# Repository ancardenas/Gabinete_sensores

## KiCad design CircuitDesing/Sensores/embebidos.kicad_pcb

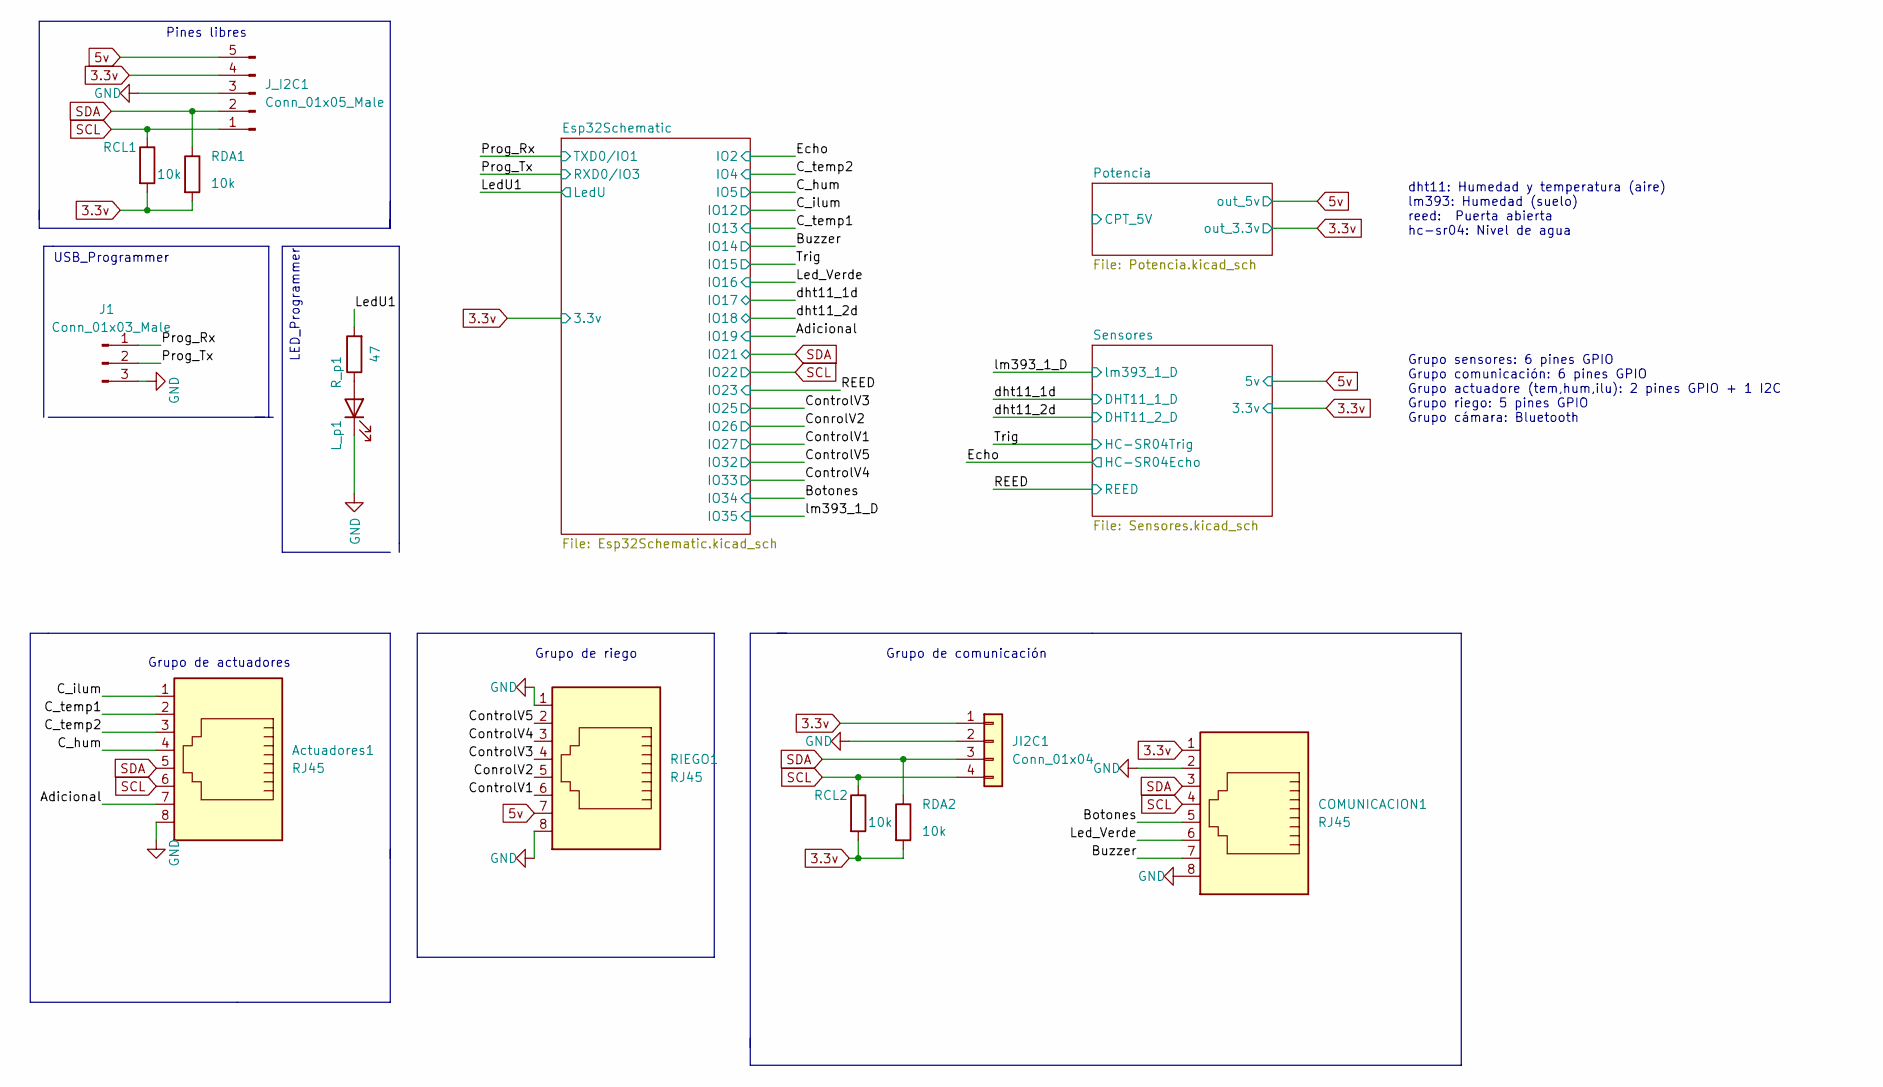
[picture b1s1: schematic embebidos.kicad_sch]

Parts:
Actuadores1: RJ45; RJ45_Amphenol_54602-x08_Horizontal
COMUNICACION1: RJ45; RJ45_Amphenol_54602-x08_Horizontal
J1: Conn_01x03_Male; PinHeader_1x03_P2.54mm_Vertical
JI2C1: Conn_01x04; JST_EH_B4B-EH-A_1x04_P2.50mm_Vertical
J_I2C1: Conn_01x05_Male; PinSocket_1x05_P2.54mm_Horizontal
L_p1: LED; LED_0805_2012Metric_Pad1.15x1.40mm_HandSolder
RCL1, RCL2: 10k; R_0805_2012Metric_Pad1.20x1.40mm_HandSolder
RDA1, RDA2: 10k; R_0805_2012Metric_Pad1.20x1.40mm_HandSolder
RIEGO1: RJ45; RJ45_Amphenol_54602-x08_Horizontal
R_p1: 47; R_0805_2012Metric_Pad1.20x1.40mm_HandSolder

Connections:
3.3v: COMUNICACION1.1, JI2C1.1, J_I2C1.4, RCL1.2, RCL2.2, RDA1.2, RDA2.2; also elsewhere on the board
5v: J_I2C1.5, RIEGO1.7; also elsewhere on the board
/Adicional: Actuadores1.7; also elsewhere on the board
/Botones: COMUNICACION1.5; also elsewhere on the board
/Buzzer: COMUNICACION1.7; also elsewhere on the board
/C_hum: Actuadores1.4; also elsewhere on the board
/C_ilum: Actuadores1.1; also elsewhere on the board
/C_temp1: Actuadores1.2; also elsewhere on the board
/C_temp2: Actuadores1.3; also elsewhere on the board
/ConrolV2: RIEGO1.5; also elsewhere on the board
/ControlV1: RIEGO1.6; also elsewhere on the board
/ControlV3: RIEGO1.4; also elsewhere on the board
/ControlV4: RIEGO1.3; also elsewhere on the board
/ControlV5: RIEGO1.2; also elsewhere on the board
/LedU1: R_p1.2; also elsewhere on the board
/Led_Verde: COMUNICACION1.6; also elsewhere on the board
/Prog_Rx: J1.1; also elsewhere on the board
/Prog_Tx: J1.2; also elsewhere on the board
GND: Actuadores1.8, COMUNICACION1.2, COMUNICACION1.8, J1.3, JI2C1.2, J_I2C1.3, L_p1.1 (K), RIEGO1.1, RIEGO1.8; also elsewhere on the board
unnamed: L_p1.2 (A), R_p1.1
SCL: Actuadores1.6, COMUNICACION1.4, JI2C1.4, J_I2C1.1, RCL1.1, RCL2.1; also elsewhere on the board
SDA: Actuadores1.5, COMUNICACION1.3, JI2C1.3, J_I2C1.2, RDA1.1, RDA2.1; also elsewhere on the board

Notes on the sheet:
Grupo sensores: 6 pines GPIO Grupo comunicación: 6 pines GPIO Grupo actuadore (tem,hum,ilu): 2 pines GPIO + 1 I2C Grupo riego: 5 pines GPIO Grupo cámara: Bluetooth
USB_Programmer
Grupo de actuadores
LED_Programmer
Pines libres
Grupo de comunicación
dht11: Humedad y temperatura (aire) lm393: Humedad (suelo) reed: Puerta abierta hc-sr04: Nivel de agua
Grupo de riego

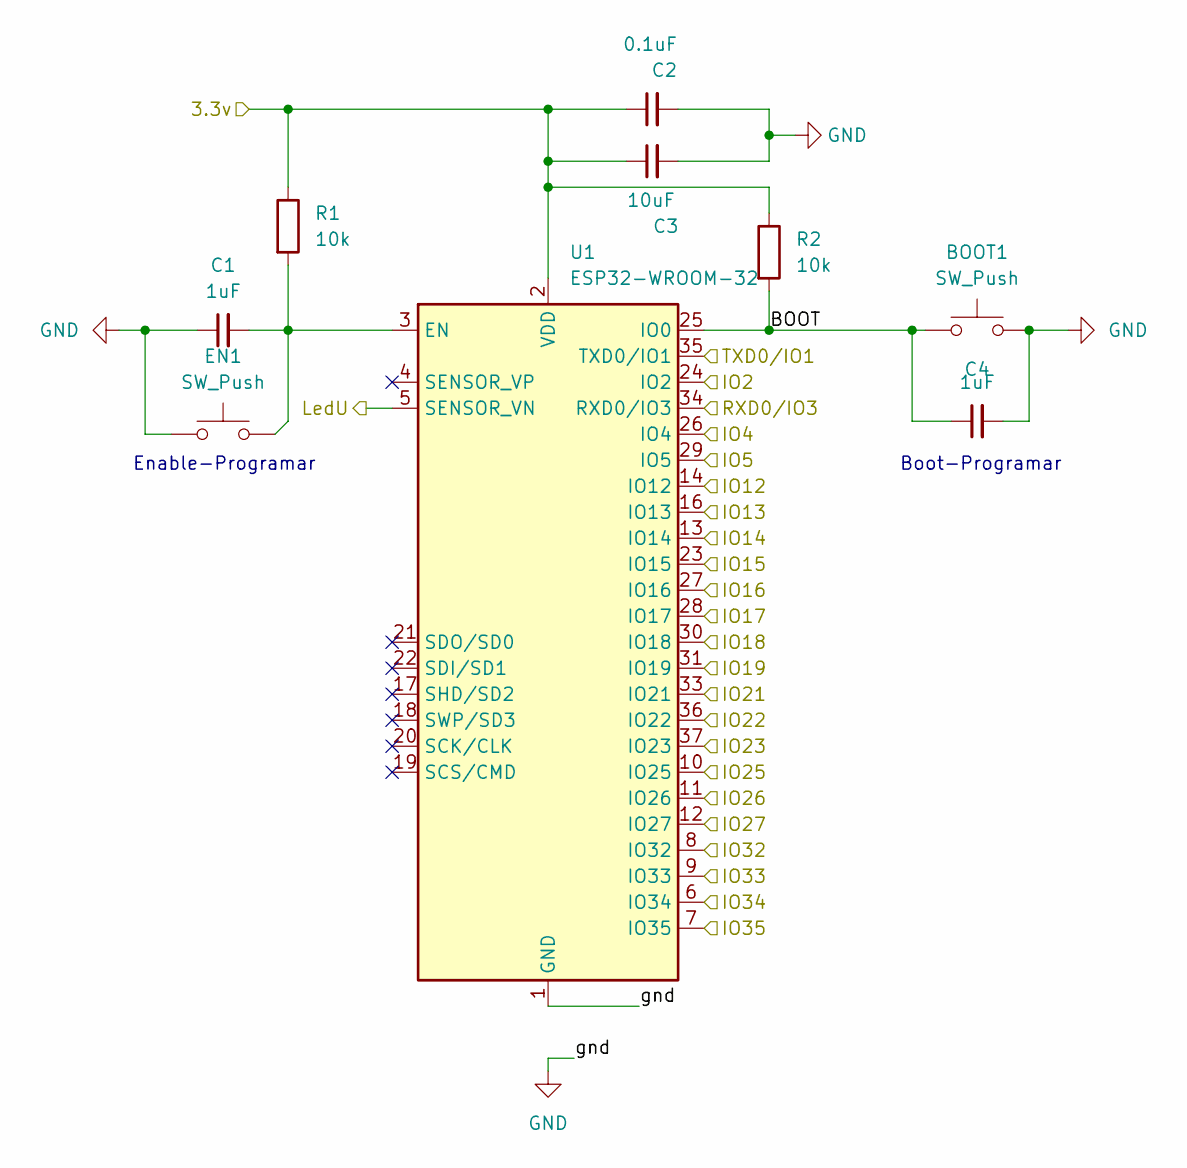
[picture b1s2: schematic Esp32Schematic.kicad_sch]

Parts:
BOOT1: SW_Push; SW_Push_1P1T_NO_6x6mm_H9.5mm
C1, C4: 1uF; C_0603_1608Metric_Pad1.08x0.95mm_HandSolder
C2: 0.1uF; C_0603_1608Metric_Pad1.08x0.95mm_HandSolder
C3: 10uF; C_0603_1608Metric_Pad1.08x0.95mm_HandSolder
EN1: SW_Push; SW_Push_1P1T_NO_6x6mm_H9.5mm
R1, R2: 10k; R_0603_1608Metric_Pad0.98x0.95mm_HandSolder
U1: ESP32-WROOM-32

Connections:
3.3v: C2.1, C3.1, R1.1, R2.1, U1.2 (VDD); also elsewhere on the board
/Adicional: U1.31 (IO19); also elsewhere on the board
/Botones: U1.6 (IO34); also elsewhere on the board
/Buzzer: U1.13 (IO14); also elsewhere on the board
/C_hum: U1.29 (IO5); also elsewhere on the board
/C_ilum: U1.14 (IO12); also elsewhere on the board
/C_temp1: U1.16 (IO13); also elsewhere on the board
/C_temp2: U1.26 (IO4); also elsewhere on the board
/ConrolV2: U1.11 (IO26); also elsewhere on the board
/ControlV1: U1.12 (IO27); also elsewhere on the board
/ControlV3: U1.10 (IO25); also elsewhere on the board
/ControlV4: U1.9 (IO33); also elsewhere on the board
/ControlV5: U1.8 (IO32); also elsewhere on the board
/Echo: U1.24 (IO2); also elsewhere on the board
/Esp32Schematic/BOOT: BOOT1.1, C4.1, R2.2, U1.25 (IO0)
/LedU1: U1.5 (SENSOR_VN); also elsewhere on the board
/Led_Verde: U1.27 (IO16); also elsewhere on the board
/Prog_Rx: U1.35 (TXD0/IO1); also elsewhere on the board
/Prog_Tx: U1.34 (RXD0/IO3); also elsewhere on the board
/REED: U1.37 (IO23); also elsewhere on the board
/Trig: U1.23 (IO15); also elsewhere on the board
/dht11_1d: U1.28 (IO17); also elsewhere on the board
/dht11_2d: U1.30 (IO18); also elsewhere on the board
/lm393_1_D: U1.7 (IO35); also elsewhere on the board
GND: BOOT1.2, C1.1, C2.2, C3.2, C4.2, EN1.1, U1.1 (GND), U1.15 (GND), U1.38 (GND), U1.39 (GND); also elsewhere on the board
unnamed: C1.2, EN1.2, R1.2, U1.3 (EN)
SCL: U1.36 (IO22); also elsewhere on the board
SDA: U1.33 (IO21); also elsewhere on the board

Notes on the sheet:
Enable-Programar
Boot-Programar

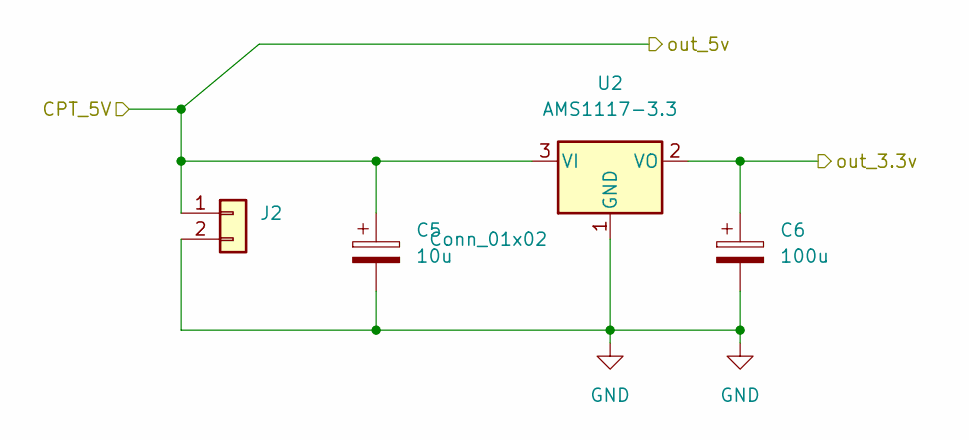
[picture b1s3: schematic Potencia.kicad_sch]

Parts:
C5: 10u; C_0603_1608Metric_Pad1.08x0.95mm_HandSolder
C6: 100u; C_0603_1608Metric_Pad1.08x0.95mm_HandSolder
J2: Conn_01x02; TerminalBlock_bornier-2_P5.08mm
U2: AMS1117-3.3; SOT-223-3_TabPin2

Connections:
3.3v: C6.1, U2.2 (VO); also elsewhere on the board
5v: C5.1, J2.1, U2.3 (VI); also elsewhere on the board
GND: C5.2, C6.2, J2.2, U2.1 (GND); also elsewhere on the board

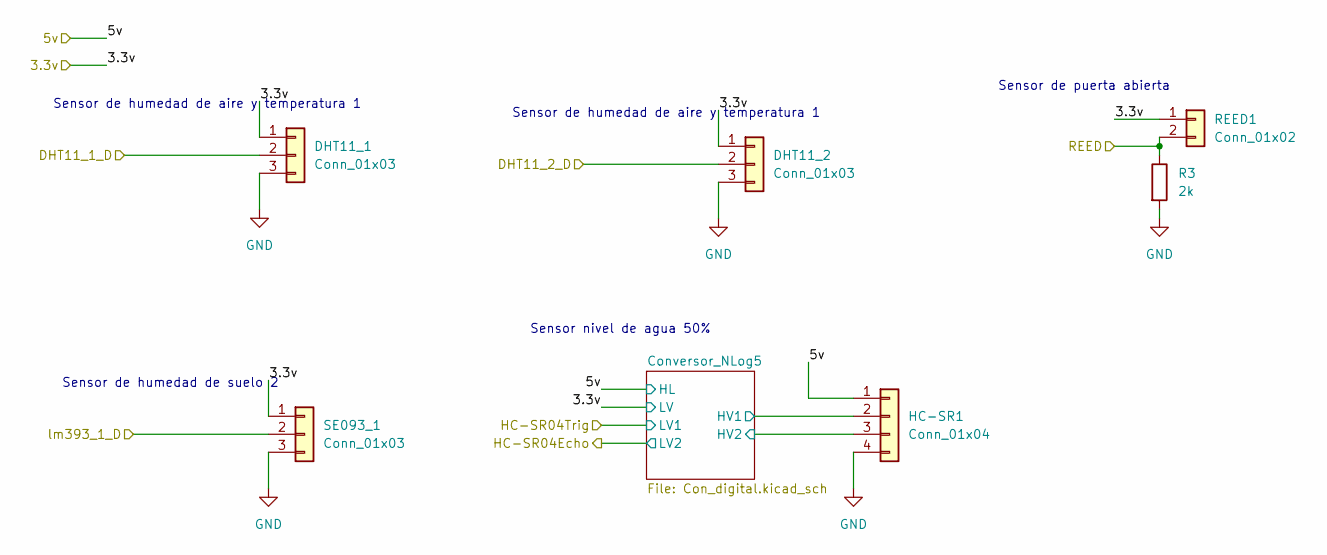
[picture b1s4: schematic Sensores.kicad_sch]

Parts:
DHT11_1, DHT11_2: Conn_01x03; JST_EH_B3B-EH-A_1x03_P2.50mm_Vertical
HC-SR1: Conn_01x04; JST_EH_B4B-EH-A_1x04_P2.50mm_Vertical
R3: 2k; R_0603_1608Metric_Pad0.98x0.95mm_HandSolder
REED1: Conn_01x02; JST_EH_B2B-EH-A_1x02_P2.50mm_Vertical
SE093_1: Conn_01x03; JST_EH_B3B-EH-A_1x03_P2.50mm_Vertical

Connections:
3.3v: DHT11_1.1, DHT11_2.1, REED1.1, SE093_1.1; also elsewhere on the board
5v: HC-SR1.1; also elsewhere on the board
/REED: R3.1, REED1.2; also elsewhere on the board
/Sensores/Conversor_NLog5/HV1: HC-SR1.2; also elsewhere on the board
/Sensores/Conversor_NLog5/HV2: HC-SR1.3; also elsewhere on the board
/dht11_1d: DHT11_1.2; also elsewhere on the board
/dht11_2d: DHT11_2.2; also elsewhere on the board
/lm393_1_D: SE093_1.2; also elsewhere on the board
GND: DHT11_1.3, DHT11_2.3, HC-SR1.4, R3.2, SE093_1.3; also elsewhere on the board

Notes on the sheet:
Sensor de humedad de aire y temperatura 1
Sensor nivel de agua 50%
Sensor de humedad de suelo 2
Sensor de puerta abierta

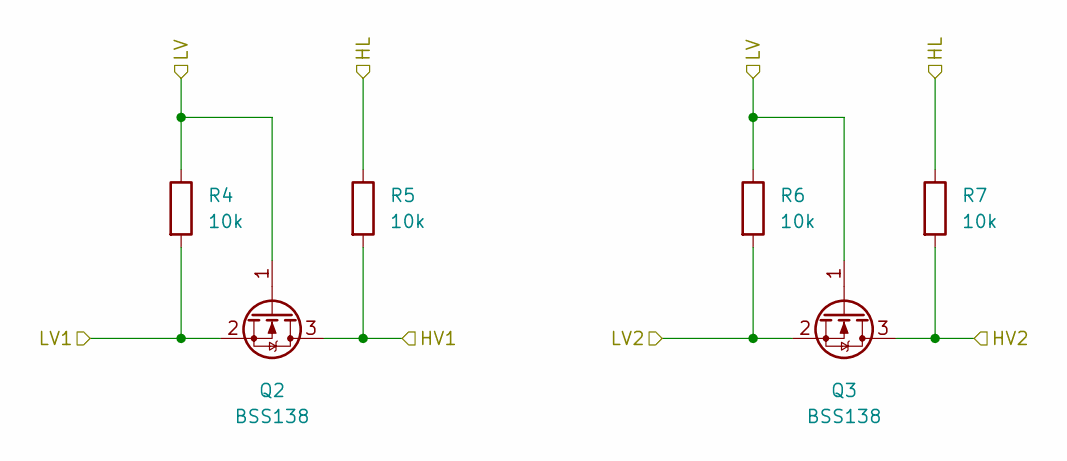
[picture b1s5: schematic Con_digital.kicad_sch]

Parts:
Q2, Q3: BSS138; SOT-23
R4, R5, R6, R7: 10k; R_0603_1608Metric_Pad0.98x0.95mm_HandSolder

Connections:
3.3v: Q2.1 (G), Q3.1 (G), R4.1, R6.1; also elsewhere on the board
5v: R5.1, R7.1; also elsewhere on the board
/Echo: Q3.2 (S), R6.2; also elsewhere on the board
/Sensores/Conversor_NLog5/HV1: Q2.3 (D), R5.2; also elsewhere on the board
/Sensores/Conversor_NLog5/HV2: Q3.3 (D), R7.2; also elsewhere on the board
/Trig: Q2.2 (S), R4.2; also elsewhere on the board

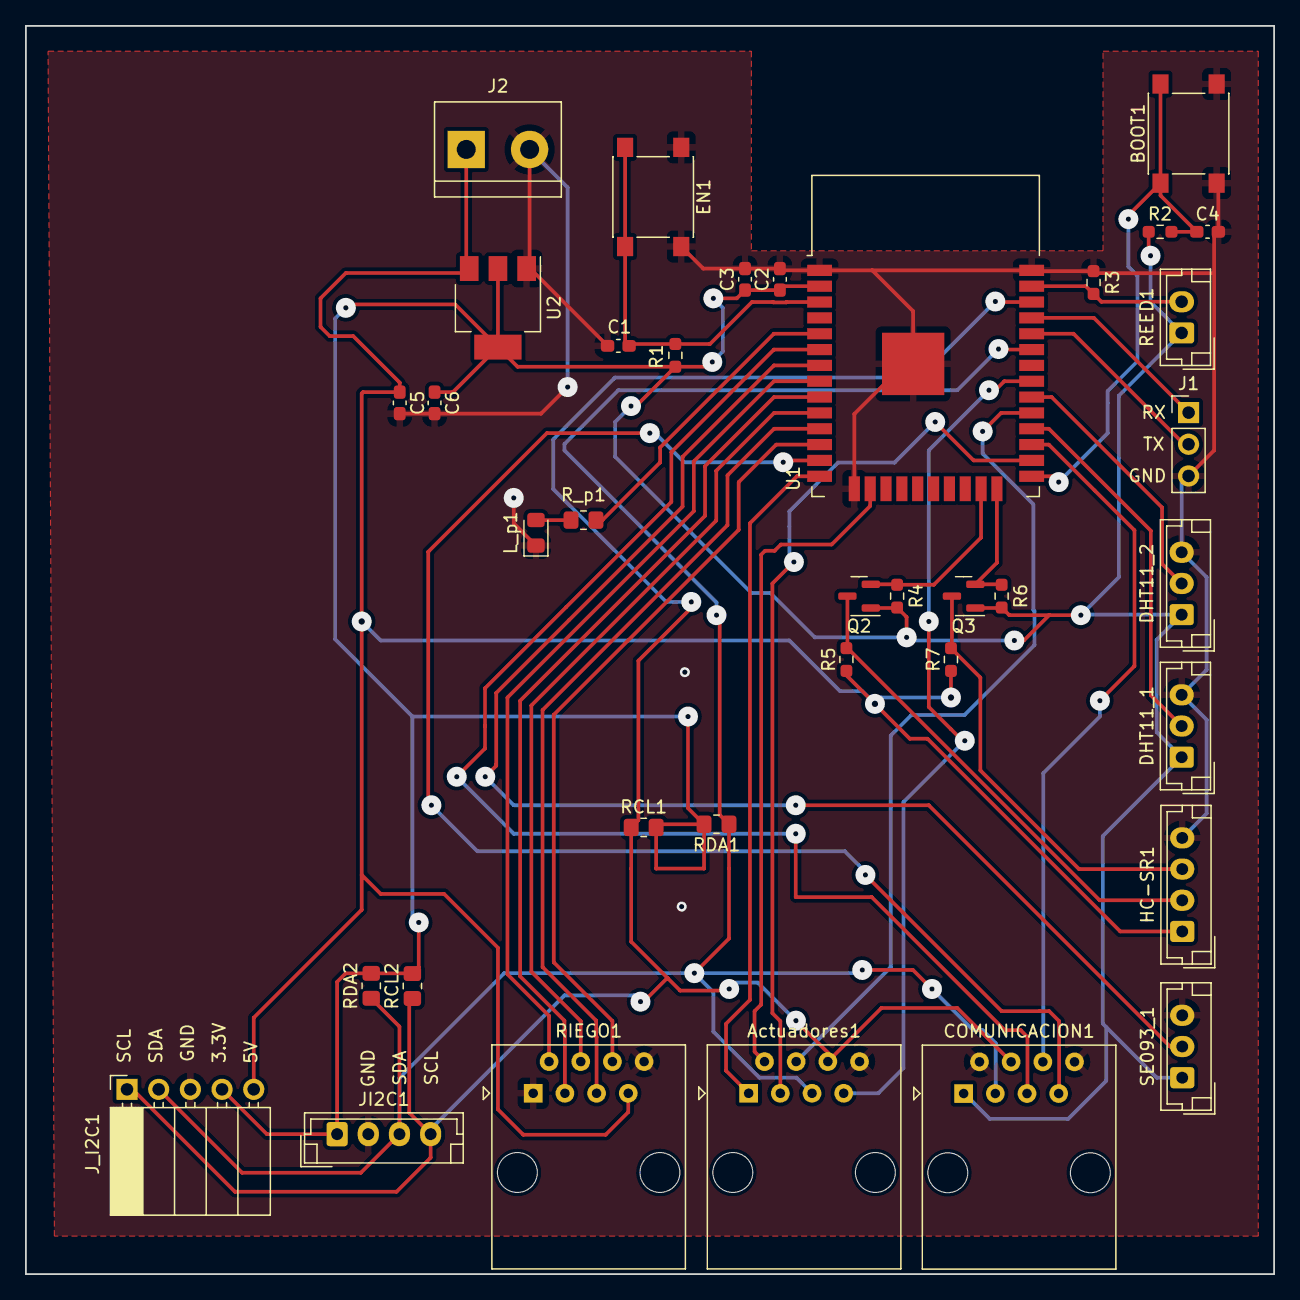
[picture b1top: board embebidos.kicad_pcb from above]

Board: 2 copper layers, 100.1 x 100.1 mm, 37 parts (0 on the bottom side), 32 nets.

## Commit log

2022-09-28 Circuito Base
2022-09-28 Eliminado Actuadores
2022-09-28 Conector REED SWITCH PARA PUERTA
2022-10-03 Actualizaciones de pines (Ultrasonido)
    Cambios en la ubicación de pines para conexión con otros grupos.
2022-10-13 UnSoloUltrasonido
2022-10-14 Modificaciones generales
    Modificaciones a esquemático, interacción con otros grupos, sistema de potencia.
2022-10-15 Huellas
2022-10-16 Listo para Ruteo
    Cambios en programador, led usuario, pines 34 35 (solo entrada)
2022-10-16 Ruteo listo
2022-10-16 Arreglo error de ruteo
2022-10-17 Coversores lógicos + alertas + cambios genrales
    Coversores lógicos + alertas + cambios generales
2022-10-17 Cambio 3.3V en alertas
    Cambio 3.3V en alertas
2022-10-17 Condensadores LDO
    Condensadores LDO
2022-10-17 Ruteo2.0
2022-10-20 Ruteo plano de tierra
2022-11-27 Programacion
2022-11-27 modulos de sensor humedad y ultrasonido
2022-11-28 sensor de humedad del suelo y ultrasonido modulares
    este si
2022-11-28 Carpeta Perifericos
    .
2022-12-01 Modularizacion del codigo
    Se agregaron los modulos, dht, vetilador
2022-12-01 Integracion Pantalla
2022-12-01 gitignore
2022-12-05 integración con la comunicaccion
    Integración de la comunicación wifi en el archivo de intento5
2022-12-05 Comunicaciones añadidas
2022-12-05 Reducir Tamaño
